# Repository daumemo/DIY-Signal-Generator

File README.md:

# DIY-Signal-Generator

A device, used for generating electrical signals. More infromation: https://daumemo.com/finished-diy-portable-wi-fi-function-generator-part-17

Repository includes all files: firmware code, schematics, PCB files.
STL files for the enclosure can be found here: https://www.thingiverse.com/thing:4596954

Device's specification:
- 3.5 inch IPS LCD with capacitive touch panel
- 2200 mAh Li-Po battery
- ESP-32 MCU
- AD9833 for sine and triangle waveform generation (up to 25 MHz)
- Square wave and PWM generated by the MCU (up to 5 MHz)
- The device can be controlled through LCD or WEB interface
- For WEB control, the device can connect to a Wi-Fi or it can create its own Wi-Fi Access Point
- Output signal’s offset range: -8V … +8V
- Output signal’s amplitude range: 0 … 9V (sine, triangle), 0 … 5.5V (square). PWM output: 3V.
- Battery charging time: <2 hours
- Working time (Wi-Fi on, output relay ON, maximum LCD brightness): around 6 hours
- USB Type C port for charging, 2 SMA ports for signal output, 1 ON/OFF switch, LED charging indicator

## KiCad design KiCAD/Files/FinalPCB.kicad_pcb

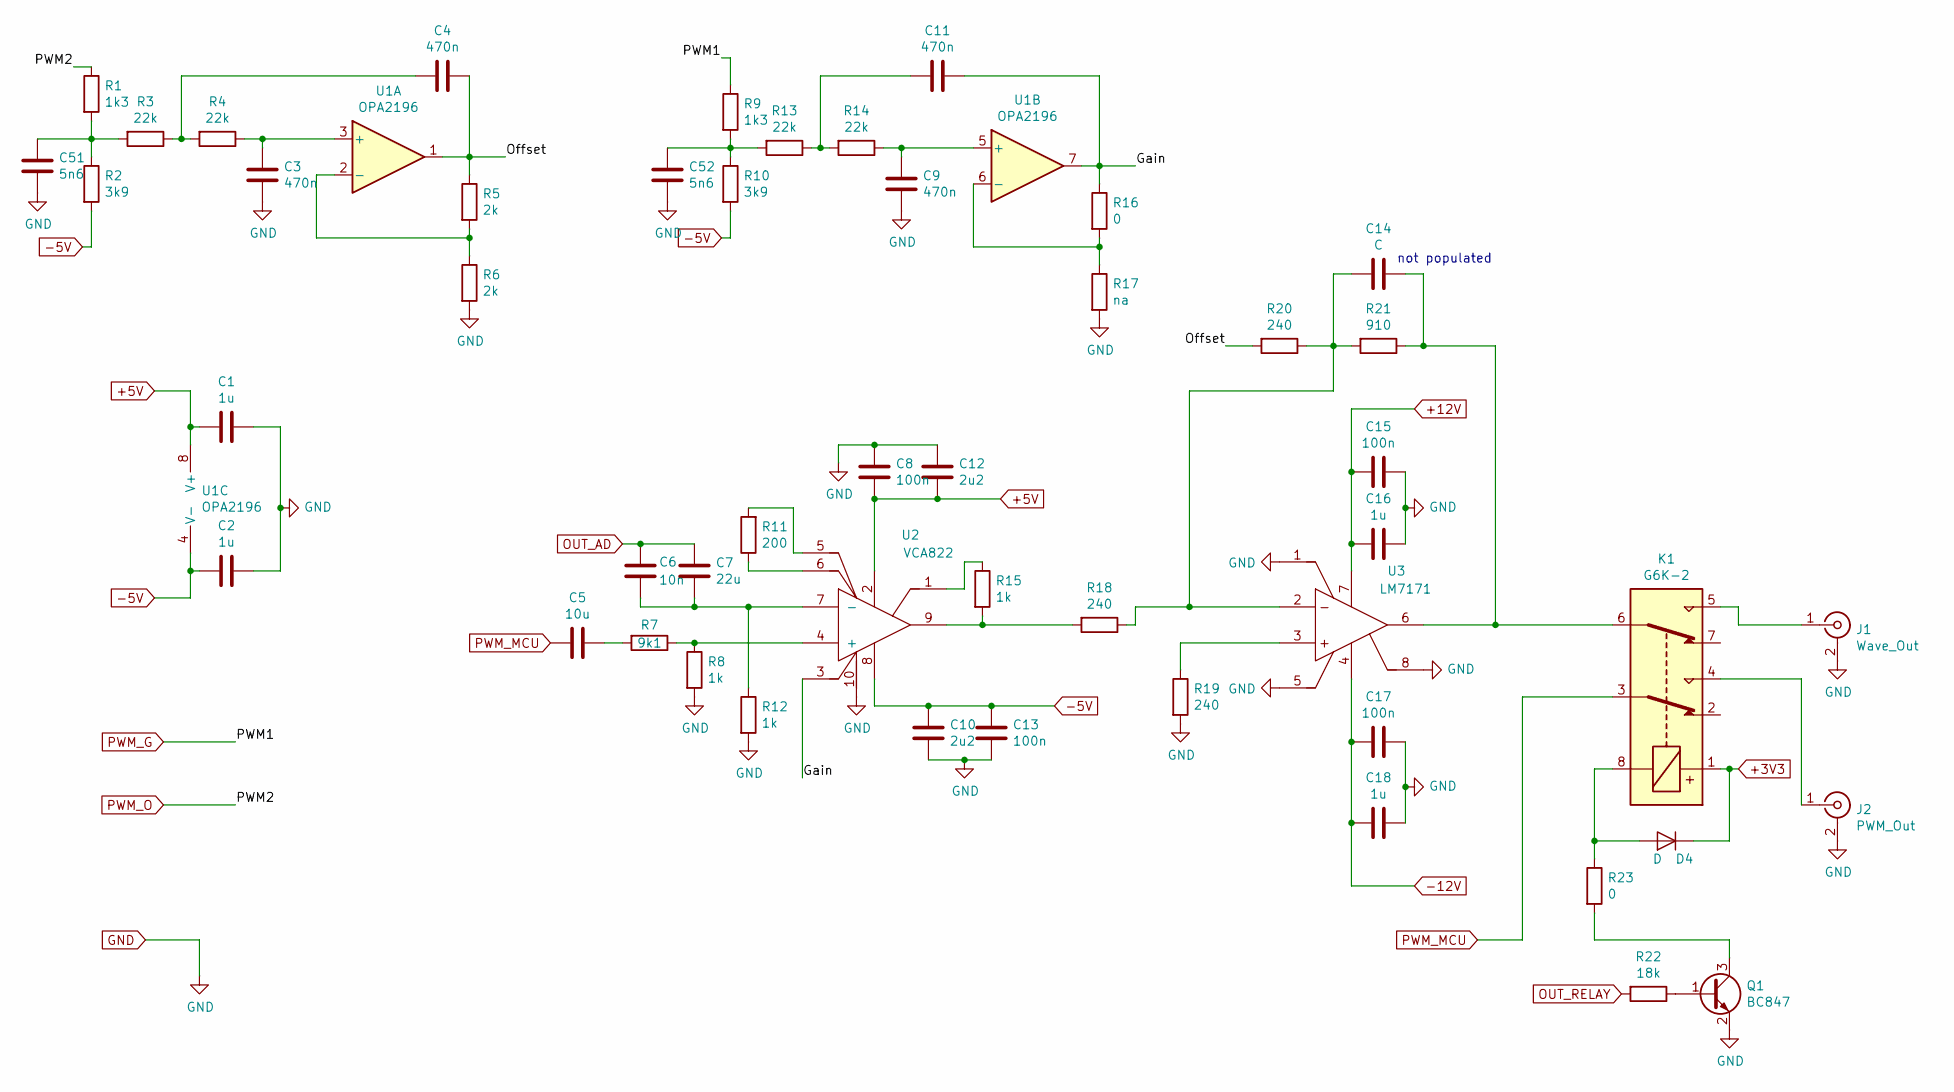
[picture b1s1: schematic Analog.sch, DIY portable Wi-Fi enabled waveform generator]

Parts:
C1, C2, C16, C18: 1u; C_0603
C3, C4, C9, C11: 470n; C_0603
C5: 10u; C_0603
C6: 10n; C_0603
C7: 22u; C_0603
C8, C13, C15, C17: 100n; C_0603
C10, C12: 2u2; C_0603
C14: C; C_0603
C51, C52: 5n6; C_0603
D4: D; D_SOD-123
J1: Wave_Out; SMA_Samtec_SMA-J-P-X-ST-EM1_EdgeMount
J2: PWM_Out; SMA_Samtec_SMA-J-P-X-ST-EM1_EdgeMount
K1: G6K-2; Relay_DPDT_Omron_G6K-2F-Y
Q1: BC847; SOT-23
R1, R9: 1k3; R_0603
R2, R10: 3k9; R_0603
R3, R4, R13, R14: 22k; R_0603
R5, R6: 2k; R_0603
R7: 9k1; R_0603
R8, R12, R15: 1k; R_0603
R11: 200; R_0603
R16: 0; R_0603
R17: na; R_0603
R18, R19, R20: 240; R_0603
R21: 910; R_0603
R22: 18k; R_0603
R23: 0; R_0805
U1: OPA2196; SOIC-8_3.9x4.9mm_Pitch1.27mm
U2: VCA822; MSOP-10_3x3mm_Pitch0.5mm
U3: LM7171; SOIC-8_3.9x4.9mm_Pitch1.27mm

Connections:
+3V3: D4.1 (K), K1.1; also elsewhere on the board
+5V: C1.2, C8.2, C12.2, U1.8 (V+), U2.2; also elsewhere on the board
+12V: C15.2, C16.2, U3.7; also elsewhere on the board
-5V: C2.2, C10.1, C13.1, R2.2, R10.2, U1.4 (V-), U2.8; also elsewhere on the board
-12V: C17.2, C18.2, U3.4; also elsewhere on the board
/Analog/Gain: C11.1, R16.1, U1.7, U2.3
/Analog/Offset: C4.1, R5.1, R20.2, U1.1
GND: C1.1, C2.1, C3.2, C8.1, C9.2, C10.2, C12.1, C13.2, C15.1, C16.1, C17.1, C18.1, C51.2, C52.2, J1.2 (Ext), J2.2 (Ext), Q1.2 (E), R6.2, R8.2, R12.2, R17.2, R19.2, U2.10, U3.1, U3.5, U3.8; also elsewhere on the board
unnamed: C3.1, R4.1, U1.3 (+)
unnamed: C4.2, R3.1, R4.2
unnamed: C5.1, R7.2
unnamed: C6.2, C7.2, R12.1, U2.7 (-)
unnamed: C9.1, R14.1, U1.5 (+)
unnamed: C11.2, R13.1, R14.2
unnamed: C14.1, K1.6, R21.1, U3.6
unnamed: C14.2, R18.1, R20.1, R21.2, U3.2
unnamed: C51.1, R1.2, R2.1, R3.2
unnamed: C52.1, R9.2, R10.1, R13.2
unnamed: D4.2 (A), K1.8, R23.1
unnamed: J1.1 (In), K1.5
unnamed: J2.1 (In), K1.4
unnamed: Q1.1 (B), R22.1
unnamed: Q1.3 (C), R23.2
unnamed: R5.2, R6.1, U1.2 (-)
unnamed: R7.1, R8.1, U2.4 (+)
unnamed: R11.1, U2.6
unnamed: R11.2, U2.5
unnamed: R15.1, U2.1
unnamed: R15.2, R18.2, U2.9
unnamed: R16.2, R17.1, U1.6 (-)
unnamed: R19.1, U3.3
OUT_AD: C6.1, C7.1; also elsewhere on the board
OUT_RELAY: R22.2; also elsewhere on the board
PWM_G: R9.1; also elsewhere on the board
PWM_MCU: C5.2, K1.3; also elsewhere on the board
PWM_O: R1.1; also elsewhere on the board

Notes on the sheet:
not populated

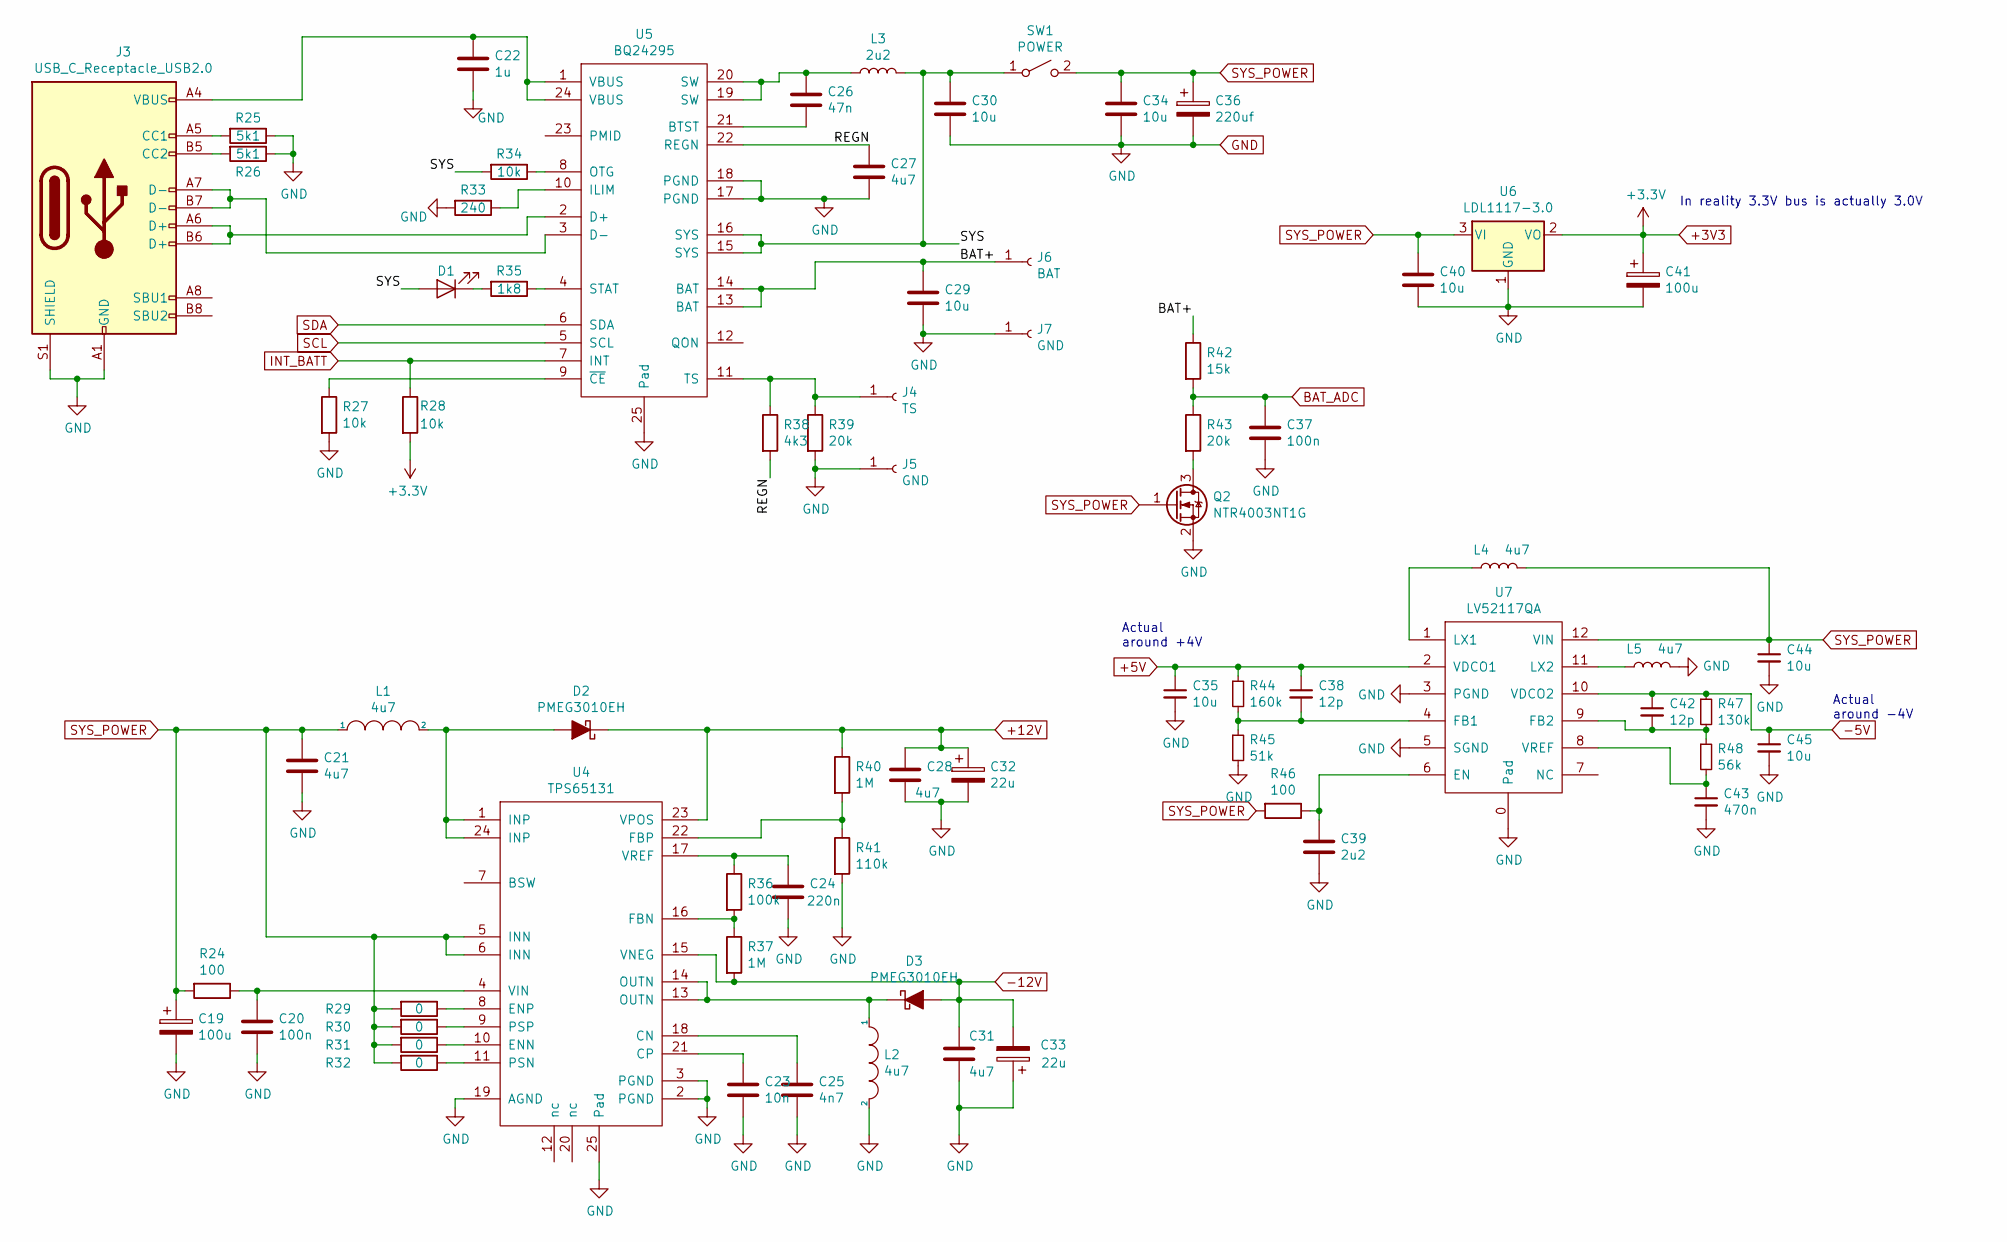
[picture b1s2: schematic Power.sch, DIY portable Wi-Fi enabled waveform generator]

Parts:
C19, C41: 100u; CP_Tantalum_Case-B_EIA-3528-21_Reflow
C20, C37: 100n; C_0603
C21, C27: 4u7; C_0603
C22: 1u; C_0603
C23: 10n; C_0603
C24: 220n; C_0603
C25: 4n7; C_0603
C26: 47n; C_0603
C28, C31: 4u7; C_0805
C29, C30, C34, C35, C40, C44, C45: 10u; C_0603
C32, C33: 22u; CP_Tantalum_Case-B_EIA-3528-21_Reflow
C36: 220uf; CP_Tantalum_Case-C_EIA-6032-28_Reflow
C38, C42: 12p; C_0603
C39: 2u2; C_0603
C43: 470n; C_0603
D1: LED; LED_0603
D2, D3: PMEG3010EH; D_SOD-123
J3: USB_C_Receptacle_USB2.0; HRO-TYPE-C-31-M-12-HandSoldering
J4: TS; Measurement_Point_Square-SMD-Pad_Big
J5, J7: GND; Measurement_Point_Square-SMD-Pad_Big
J6: BAT; Measurement_Point_Square-SMD-Pad_Big
L1, L2, L4, L5: 4u7; L_Taiyo-Yuden_NR-40xx_HandSoldering
L3: 2u2; L_Taiyo-Yuden_NR-40xx_HandSoldering
Q2: NTR4003NT1G; SOT-23
R24, R46: 100; R_0603
R25, R26: 5k1; R_0603
R27, R28, R34: 10k; R_0603
R29, R30, R31, R32: 0; R_0603
R33: 240; R_0603
R35: 1k8; R_0603
R36: 100k; R_0603
R37, R40: 1M; R_0603
R38: 4k3; R_0603
R39, R43: 20k; R_0603
R41: 110k; R_0603
R42: 15k; R_0603
R44: 160k; R_0603
R45: 51k; R_0603
R47: 130k; R_0603
R48: 56k; R_0603
SW1: POWER; Switch
U4: TPS65131; QFN-24-1EP_4x4mm_Pitch0.5mm
U5: BQ24295; QFN-24-1EP_4x4mm_Pitch0.5mm
U6: LDL1117-3.0; SOT-223-3_TabPin2
U7: LV52117QA

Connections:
+3V3: C41.1, R28.2, U6.2 (VO); also elsewhere on the board
+5V: C35.1, C38.1, R44.1, U7.2 (VDCO1); also elsewhere on the board
+12V: C28.1, C32.1, D2.1 (K), R40.1, U4.23 (VPOS); also elsewhere on the board
-5V: C42.1, C45.1, R47.1, U7.10 (VDCO2); also elsewhere on the board
-12V: C31.1, C33.2, D3.2 (A), R37.2, U4.15 (VNEG); also elsewhere on the board
/Power/BAT+: C29.1, J6.1, R42.1, U5.13 (BAT), U5.14 (BAT)
/Power/REGN: C27.1, R38.2, U5.22 (REGN)
/Power/SYS: C30.1, D1.2 (A), L3.2, R34.2, SW1.1 (A), U5.15 (SYS), U5.16 (SYS)
BAT_ADC: C37.1, R42.2, R43.1; also elsewhere on the board
GND: C19.2, C20.2, C21.2, C22.2, C23.2, C24.2, C25.2, C27.2, C28.2, C29.2, C30.2, C31.2, C32.2, C33.1, C34.2, C35.2, C36.2, C37.2, C39.2, C40.2, C41.2, C43.2, C44.2, C45.2, J3.A1 (GND), J3.A12 (GND), J3.B1 (GND), J3.B12 (GND), J3.S1 (SHIELD), J5.1, J7.1, L2.2, L5.2, Q2.2 (S), R25.1, R26.1, R27.2, R33.2, R39.2, R41.2, R45.2, U4.2 (PGND), U4.3 (PGND), U4.19 (AGND), U4.25 (Pad), U5.17 (PGND), U5.18 (PGND), U5.25 (Pad), U6.1 (GND), U7.0 (Pad), U7.3 (PGND), U7.5 (SGND); also elsewhere on the board
INT_BATT: R28.1, U5.7 (INT); also elsewhere on the board
unnamed: C20.1, R24.1, U4.4 (VIN)
unnamed: C22.1, J3.A4 (VBUS), J3.A9 (VBUS), J3.B4 (VBUS), J3.B9 (VBUS), U5.1 (VBUS), U5.24 (VBUS)
unnamed: C23.1, U4.21 (CP)
unnamed: C24.1, R36.1, U4.17 (VREF)
unnamed: C25.1, U4.18 (CN)
unnamed: C26.1, L3.1, U5.19 (SW), U5.20 (SW)
unnamed: C26.2, U5.21 (BTST)
unnamed: C38.2, R44.2, R45.1, U7.4 (FB1)
unnamed: C39.1, R46.1, U7.6 (EN)
unnamed: C42.2, R47.2, R48.1, U7.9 (FB2)
unnamed: C43.1, R48.2, U7.8 (VREF)
unnamed: D1.1 (K), R35.2
unnamed: D2.2 (A), L1.2, U4.1 (INP), U4.24 (INP)
unnamed: D3.1 (K), L2.1, U4.13 (OUTN), U4.14 (OUTN)
unnamed: J3.A5 (CC1), R25.2
unnamed: J3.A6 (D+), J3.B6 (D+), U5.2 (D+)
unnamed: J3.A7 (D-), J3.B7 (D-), U5.3 (D-)
unnamed: J3.B5 (CC2), R26.2
unnamed: J4.1, R38.1, R39.1, U5.11 (TS)
unnamed: L4.1, U7.1 (LX1)
unnamed: L5.1, U7.11 (LX2)
unnamed: Q2.3 (D), R43.2
unnamed: R27.1, U5.9 (~CE)
unnamed: R29.1, U4.8 (ENP)
unnamed: R30.1, U4.9 (PSP)
unnamed: R31.1, U4.10 (ENN)
unnamed: R32.1, U4.11 (PSN)
unnamed: R33.1, U5.10 (ILIM)
unnamed: R34.1, U5.8 (OTG)
unnamed: R35.1, U5.4 (STAT)
unnamed: R36.2, R37.1, U4.16 (FBN)
unnamed: R40.2, R41.1, U4.22 (FBP)
SCL: U5.5 (SCL); also elsewhere on the board
SDA: U5.6 (SDA); also elsewhere on the board
SYS_POWER: C19.1, C21.1, C34.1, C36.1, C40.1, C44.1, L1.1, L4.2, Q2.1 (G), R24.2, R29.2, R30.2, R31.2, R32.2, R46.2, SW1.2 (B), U4.5 (INN), U4.6 (INN), U6.3 (VI), U7.12 (VIN)

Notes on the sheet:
In reality 3.3V bus is actually 3.0V
Actual around -4V
Actual around +4V

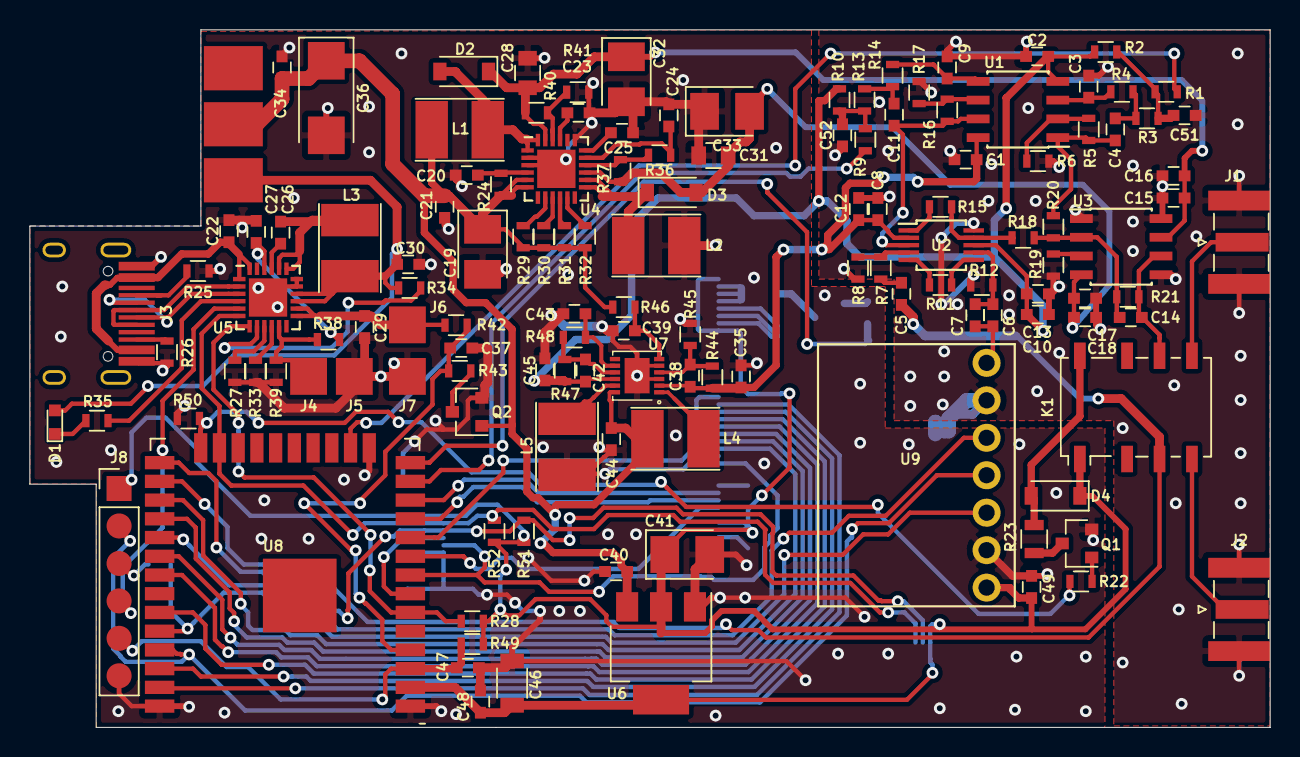
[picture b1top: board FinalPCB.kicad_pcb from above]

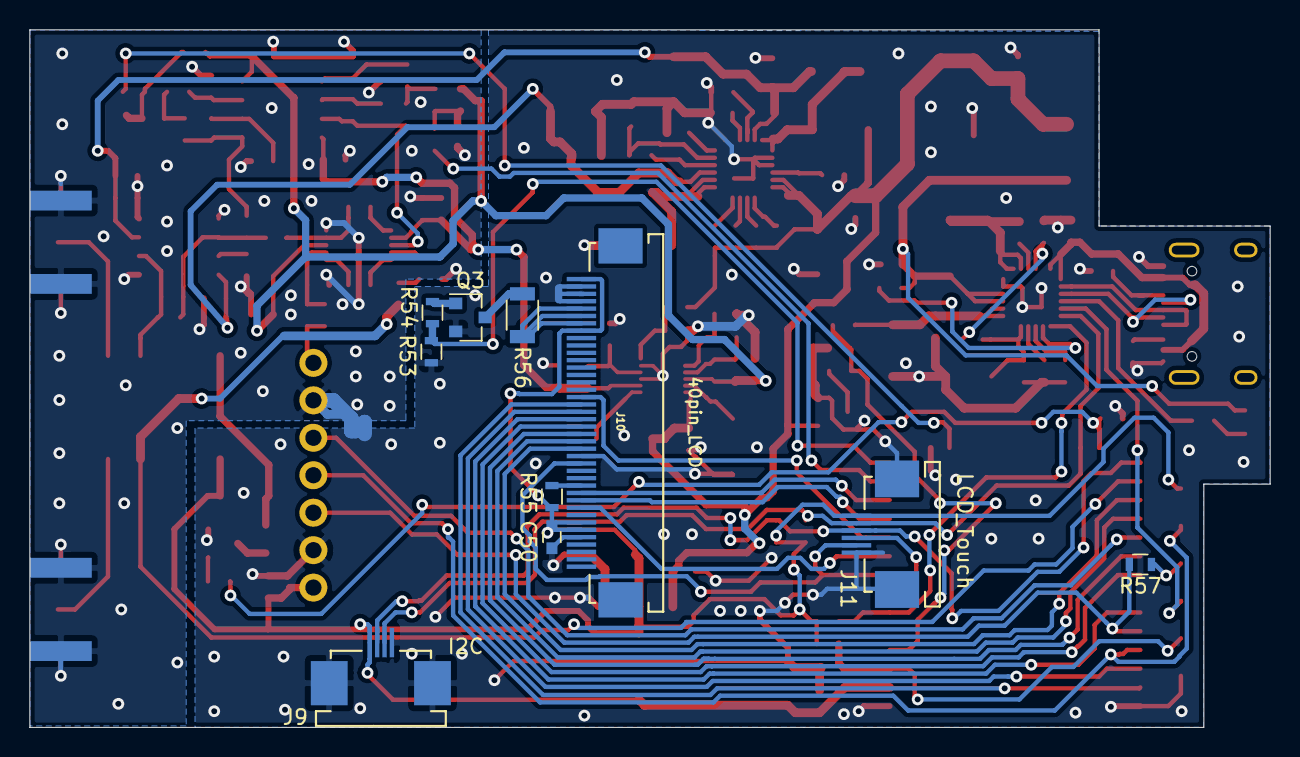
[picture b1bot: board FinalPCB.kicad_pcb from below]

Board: 2 copper layers, 84.1 x 47.3 mm, 143 parts (10 on the bottom side), 99 nets.

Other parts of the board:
C46: 100u; C_1206
C47: 10n; C_0603
C48, C50: 10u; C_0603
C49: 1u; C_0603
J8: UART; Pin_Header_Straight_1x06_Pitch2.54mm
J9: I2C; User_FPC_4pin_05pitch_bot_cont
J10: 40pin_LCD; User_FPC_40pin_05pitch_BottomContact
J11: LCD_Touch; User_FPC_6pin_05pitch_top_cont
Q3: NTR4003NT1G; SOT-23
R49: 12k; R_0603
R50: 10k; R_0603
R51, R52: 3k3; R_0603
R53: 1M; R_0603
R54, R55: 0; R_0603
R56: 1R; R_1206
R57: 470; R_0603
U8: ESP32-WROOM-32
U9: AD9833_module

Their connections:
+3V3: C46.1, C48.1, C49.1, C50.1, J8.1, J9.1, J10.6, J10.7, J10.33, J10.40, J11.1, R49.1, R51.1, R52.1, R55.1, U8.2, U9.1; also elsewhere on the board
/MCU/CSX: J10.9, U8.9
/MCU/D0: J10.17, U8.27
/MCU/D1: J10.18, U8.28
/MCU/D2: J10.19, U8.30
/MCU/D3: J10.20, U8.31
/MCU/D4: J10.21, U8.33
/MCU/D5: J10.22, U8.36
/MCU/D6: J10.23, U8.37
/MCU/D7: J10.24, U8.10
/MCU/DCX: J10.10, U8.11
/MCU/EN: C47.1, J8.5, R49.2, U8.3
/MCU/FSYNC_AD: U8.29, U9.5
/MCU/INT_TOUCH: J11.4, U8.7
/MCU/LED_PWM: R53.1, R54.2, U8.14
/MCU/RDX: J10.12, R55.2
/MCU/RESX: J10.15, J11.5, U8.8
/MCU/RX: R57.2, U8.34, U9.3
/MCU/SCLK_AD: J8.2, U8.35, U9.4
/MCU/WRX: J10.11, U8.12
BAT_ADC: U8.4; also elsewhere on the board
GND: C46.2, C47.2, C48.2, C49.2, C50.2, J8.6, J9.4, J10.5, J10.16, J10.37, J10.38, J10.39, J11.6, Q3.2, R50.2, R53.2, U8.1, U8.15, U8.38, U9.2, U9.6; also elsewhere on the board
INT_BATT: U8.6; also elsewhere on the board
unnamed: J8.3, R57.1
unnamed: J10.34, J10.35, J10.36, R56.1
unnamed: Q3.1, R54.1
unnamed: Q3.3, R56.2
OUT_AD: U9.7; also elsewhere on the board
OUT_RELAY: R50.1, U8.24; also elsewhere on the board
PWM_G: U8.13; also elsewhere on the board
PWM_MCU: U8.26; also elsewhere on the board
PWM_O: U8.16; also elsewhere on the board
SCL: J8.4, J9.2, J11.3, R51.2, U8.25; also elsewhere on the board
SDA: J9.3, J11.2, R52.2, U8.23; also elsewhere on the board

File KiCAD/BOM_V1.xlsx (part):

Date: | 43977.017048611109 | additional modification 2020-09-15
Tool: | Eeschema (5.1.4)-1
NOTE: capacitor voltages specified below are recommended values - it is OK to u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
Component Count: | 141
Ref | Value | Footprint | Description | Remarks, links etc.
C1 | 1u 10V | SMD 0603 | Unpolarized capacitor
C2 | 1u 10V | SMD 0603 | Unpolarized capacitor
C3 | 470n 16V | SMD 0603 | Unpolarized capacitor
C4 | 470n 16V | SMD 0603 | Unpolarized capacitor
C5 | 10uF 6V | SMD 0603 | Unpolarized capacitor
C6 | 10n 50V | SMD 0603 | Unpolarized capacitor
C7 | 22u 6V | SMD 0603 | Unpolarized capacitor
C8 | 100n 50V | SMD 0603 | Unpolarized capacitor
C9 | 470n 16V | SMD 0603 | Unpolarized capacitor
C10 | 2u2 10V | SMD 0603 | Unpolarized capacitor
C11 | 470n 16V | SMD 0603 | Unpolarized capacitor
C12 | 2u2 10V | SMD 0603 | Unpolarized capacitor
C13 | 100n 50V | SMD 0603 | Unpolarized capacitor
C14 | not soldered in | SMD 0603 | Unpolarized capacitor (not soldered in)
C15 | 100n 50V | SMD 0603 | Unpolarized capacitor
C16 | 1u 16V | SMD 0603 | Unpolarized capacitor
C17 | 100n 50V | SMD 0603 | Unpolarized capacitor
C18 | 1u 16V | SMD 0603 | Unpolarized capacitor
C19 | 100u 6V | SMD Case-B (EIA-3528) | Polarized tantalum capacitor
C20 | 100n 50V | SMD 0603 | Unpolarized capacitor
C21 | 4u7 6V | SMD 0603 | Unpolarized capacitor
C22 | 1u 10V | SMD 0603 | Unpolarized capacitor
C23 | 10n 50V | SMD 0603 | Unpolarized capacitor
C24 | 220n 16V | SMD 0603 | Unpolarized capacitor
C25 | 4n7 50V | SMD 0603 | Unpolarized capacitor
C26 | 47n 16V | SMD 0603 | Unpolarized capacitor
C27 | 4u7 6V | SMD 0603 | Unpolarized capacitor
C28 | 4u7 16V | SMD 0805 | Unpolarized capacitor
C29 | 10u 6V | SMD 0603 | Unpolarized capacitor
C30 | 10u 6V | SMD 0603 | Unpolarized capacitor
C31 | 4u7 16V | SMD 0805 | Unpolarized capacitor
C32 | 22u 16V | SMD Case-B (EIA-3528) | Polarized tantalum capacitor
C33 | 22u 16V | SMD Case-B (EIA-3528) | Polarized tantalum capacitor
C34 | 10u 6V | SMD 0603 | Unpolarized capacitor
C35 | 10u 10V | SMD 0603 | Unpolarized capacitor
C36 | 220uf 6V | SMD Case-C (EIA-6032) | Polarized tantalum capacitor
C37 | 100n 50V | SMD 0603 | Unpolarized capacitor
C38 | 12p 50V | SMD 0603 | Unpolarized capacitor
C39 | 2u2 6V | SMD 0603 | Unpolarized capacitor
C40 | 10u 6V | SMD 0603 | Unpolarized capacitor
C41 | 100u 6V | SMD Case-B (EIA-3528) | Polarized tantalum capacitor
C42 | 12p 50V | SMD 0603 | Unpolarized capacitor
C43 | 470n 16V | SMD 0603 | Unpolarized capacitor
C44 | 10u 6V | SMD 0603 | Unpolarized capacitor
C45 | 10u 10V | SMD 0603 | Unpolarized capacitor
C46 | 100u 6V | SMD 1206 | Unpolarized capacitor
C47 | 10n 50V | SMD 0603 | Unpolarized capacitor
C48 | 10u 6V | SMD 0603 | Unpolarized capacitor
C49 | 1u 10V | SMD 0603 | Unpolarized capacitor
C50 | 10u 6V | SMD 0603 | Unpolarized capacitor
C51 | 5n6 25V | SMD 0603 | Unpolarized capacitor
C52 | 5n6 25V | SMD 0603 | Unpolarized capacitor
D1 | LED, amber | SMD LED 0603 | Light emitting diode
D2 | PMEG3010EH | SMD SOD-123 | Schottky diode | Could be used similar diode
D3 | PMEG3010EH | SMD SOD-123 | Schottky diode | Could be used similar diode
D4 | PMEG3010EH | SMD SOD-123 | Diode | Can be a regular diode in SOD-123 case
J1 | Wave_Out | SMA-J-P-X-ST-EM1_EdgeMount | coaxial connector SMA | https://www.aliexpress.com/item/32948380887.html?spm=a2g0s.9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
J2 | PWM_Out | SMA-J-P-X-ST-EM1_EdgeMount | coaxial connector SMA | https://www.aliexpress.com/item/32948380887.html?spm=a2g0s.9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
J3 | USB_C_Receptacle_USB2.0 | Type-C:HRO-TYPE-C-31-M-12-HandSoldering | USB 2.0-only Type-C Receptacle connector | https://www.aliexpress.com/item/32962977859.html?spm=a2g0s.9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
J4 | TS |  | PCB connector
J5 | GND |  | PCB connector
J6 | BAT |  | PCB connector | Lipo/Liion Battery +
J7 | GND |  | PCB connector | Lipo/Liion Battery -
J8 | UART |  | PCB connector
J9 | I2C (not soldered in) | FinalPCB:User_FPC_4pin_05pitch_bot_cont | FPC 4pin connector | Not soldered in (not used)
J10 | 40pin_LCD | FinalPCB:User_FPC_40pin_05pitch_BottomContact | FPC 40pin horizontal bottom contact connector
J11 | LCD_Touch | FinalPCB:User_FPC_6pin_05pitch_top_cont | FPC 6pin horizontal top contact connector
K1 | G6K-2F-Y | Relay_DPDT_Omron_G6K-2F-Y | Miniature 2-pole relay, Single-side Stable
L1 | 4u7 | SMD:4x4mm NRS4012T4R7MDGJ | Inductor | https://eu.mouser.com/ProductDetail/Taiyo-Yuden/NRS4012T4R7M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
L2 | 4u7 | SMD:4x4mm NRS4012T4R7MDGJ | Inductor | https://eu.mouser.com/ProductDetail/Taiyo-Yuden/NRS4012T4R7M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
L3 | 2u2 | SMD:4x4mm NRS4012T2R2MDGJ | Inductor | https://eu.mouser.com/ProductDetail/Taiyo-Yuden/NRS4012T2R2M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
L4 | 4u7 | SMD:4x4mm NRS4012T4R7MDGJ | Inductor | https://eu.mouser.com/ProductDetail/Taiyo-Yuden/NRS4012T4R7M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
L5 | 4u7 | SMD:4x4mm NRS4012T4R7MDGJ | Inductor | https://eu.mouser.com/ProductDetail/Taiyo-Yuden/NRS4012T4R7M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
Q1 | BC847C | SMD SOT-23 | 0.1A Ic, 45V Vce, NPN Transistor, SOT-23
Q2 | NTR4003NT1G | SMD SOT-23 | N-MOSFET transistor, gate/source/drain
Q3 | NTR4003NT1G | SMD SOT-23 | N-MOSFET transistor, gate/source/drain
R1 | 1k3 | SMD 0603 | Resistor
R2 | 3k9 | SMD 0603 | Resistor
R3 | 22k | SMD 0603 | Resistor
R4 | 22k | SMD 0603 | Resistor
R5 | 2k | SMD 0603 | Resistor
R6 | 2k | SMD 0603 | Resistor
R7 | 9k1 | SMD 0603 | Resistor
R8 | 1k | SMD 0603 | Resistor
R9 | 1k3 | SMD 0603 | Resistor
R10 | 3k9 | SMD 0603 | Resistor
R11 | 200 | SMD 0603 | Resistor
R12 | 1k | SMD 0603 | Resistor
R13 | 22k | SMD 0603 | Resistor
R14 | 22k | SMD 0603 | Resistor
R15 | 1k | SMD 0603 | Resistor
R16 | 0 | SMD 0603 | Resistor
R17 | not soldered in | SMD 0603 | Resistor
R18 | 240 | SMD 0603 | Resistor
R19 | 240 | SMD 0603 | Resistor
R20 | 240 | SMD 0603 | Resistor
R21 | 910 | SMD 0603 | Resistor
R22 | 18k | SMD 0603 | Resistor
R23 | 0 | SMD 0805 | Resistor
R24 | 100 | SMD 0603 | Resistor
R25 | 5k1 | SMD 0603 | Resistor
R26 | 5k1 | SMD 0603 | Resistor
R27 | 10k | SMD 0603 | Resistor
R28 | 10k | SMD 0603 | Resistor
R29 | 0 | SMD 0603 | Resistor
R30 | 0 or not soldered | SMD 0603 | Resistor | if soldered in - power saving mode
R31 | 0 | SMD 0603 | Resistor
R32 | 0 or not soldered | SMD 0603 | Resistor | if soldered in - power saving mode
R33 | 240 | SMD 0603 | Resistor
R34 | 10k | SMD 0603 | Resistor
R35 | 1k8 | SMD 0603 | Resistor
R36 | 100k | SMD 0603 | Resistor
R37 | 1M | SMD 0603 | Resistor
R38 | 4k3 | SMD 0603 | Resistor
R39 | 20k | SMD 0603 | Resistor
R40 | 1M | SMD 0603 | Resistor
R41 | 110k | SMD 0603 | Resistor
R42 | 15k | SMD 0603 | Resistor
R43 | 20k | SMD 0603 | Resistor
R44 | 160k | SMD 0603 | Resistor
R45 | 51k | SMD 0603 | Resistor
R46 | 100 | SMD 0603 | Resistor
R47 | 130k | SMD 0603 | Resistor
R48 | 56k | SMD 0603 | Resistor
R49 | 12k | SMD 0603 | Resistor
R50 | 10k | SMD 0603 | Resistor
R51 | 3k3 | SMD 0603 | Resistor
R52 | 3k3 | SMD 0603 | Resistor
R53 | 1M | SMD 0603 | Resistor
R54 | 0 | SMD 0603 | Resistor
R55 | 0 | SMD 0603 | Resistor
R56 | 1R | SMD 1206 | Resistor
R57 | 470 | SMD 0603 | Resistor
SW1 |  | FinalPCB:Switch | Single Pole Single Throw (SPST) switch | https://www.aliexpress.com/item/32852841524.html?spm=a2g0o.d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
U1 | OPA2196 | SOIC:SOIC-8_3.9x4.9mm_Pitch1.27mm | Dual SoundPlus High Performance Audio Operational Amplifiers SOIC-8
U2 | VCA822 | SSOP:MSOP-10_3x3mm_Pitch0.5mm | Variable gain operational amplifier
U3 | LM7171 | SOIC:SOIC-8_3.9x4.9mm_Pitch1.27mm | High bandwidth operational amplifier
U4 | TPS65131 | QFN-24-1EP_4x4mm_Pitch0.5mm | DC-DC converter
U5 | BQ24295 | QFN-24-1EP_4x4mm_Pitch0.5mm | Battery charging IC
U6 | LDL1117-3.0 | SOT-223-3_TabPin2 | 1A Fixed LDO Linear Regulator, 3.0V SOT-223
U7 | LV52117QA | LV52117:LV52117QA | DC-DC converter
U8 | ESP32-WROOM-32 | ESP32-WROOM-32 | RF Module, ESP32-D0WDQ6 SoC, Wi-Fi 802.11b/g/n, Bluetooth, BLE, 32-bit, 2.7-3.6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 | https://www.aliexpress.com/item/32799985552.html?spm=a2g0s.9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
U9 | AD9833_module | AD9833_module |  | https://www.aliexpress.com/item/32998169276.html?spm=a2g0o.p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
EXTERNAL COMPONENTS:
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
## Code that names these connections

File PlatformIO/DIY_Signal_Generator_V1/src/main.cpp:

/************************************************************************************
 * 
 * This is an example code used to test R61529 based LCD with FT6236 touch controller
 * connected to an ESP32 MCU through parallel(8080) interface. This code uses eSPI 
 * library
 * 
 * 
 * Note: Although you will find some files that contains R61581 in it, but be aware 
 * that those are modified files from original eSPI library to support R61529 ICs
 * (Some or all code was changed in those header files).
 * 
 * LCD Connection to the ESP32:
 * 
 * D0 -> GPIO 16
 * D1 -> GPIO 17
 * D2 -> GPIO 18
 * D3 -> GPIO 19
 * D4 -> GPIO 21
 * D5 -> GPIO 22
 * D6 -> GPIO 23
 * D7 -> GPIO 25
 * 
 * CSX -> GPIO 33
 * DCX -> GPIO 26
 * RSX -> GPIO 32
 * WRX -> GPIO 27
 * 
 * TOUCH IC connection to the ESP32:
 * 
 * SDA -> GPIO 15
 * SCL -> GPIO 14->0
 * INT -> GPIO 35
 * RST -> GPIO 32 (connected together with the LCD reset pin) 
 *
 *************************************************************************************/


#include <Arduino.h>

#include "../lib/TFT_eSPI/TFT_eSPI.h"
#include "Wire.h"

#include <WiFi.h>
#include <WiFiUdp.h>
#include <ArduinoOTA.h>
#include "ota.h"
#include <EEPROM.h>
#include <WiFiClient.h>
#include <WebServer.h>
#include <HTTPClient.h>

#include <SPI.h>

#include "../lib/AD9833/ad9833.h"
#include "bq24295.h"
#include "../lib/lvgl/src/lvgl.h"

#include "../lib/lcd_interface/lcd_interface.h"
#include "../lib/touch_drv/touch_drv.h"
#include "../lib/generator/generator.h"
#include "../lib/device/device.h"


uint64_t battMeasureTimer = 0;
int battUpdateTimer = 0;


void setup()
{
  
  Device.LoadSettings();
  
  if(Device.IsApOn() || Device.IsWiFiOn()){
    OtaSetup();
  }

  BQ24295_IC charger(15, 0, 100000);

  charger.setI2cWatchdogTimer(0);
  charger.setFastChargeCurrent(0b010000);
  charger.setPreChargeCurrent(0b0001);
  charger.setFastChargeTimer(0);
  charger.setBoostVoltage(0b1000);
  charger.enableOTG(false);

  
  touchInit();
  Wire.beginTransmission(0x38);
  Wire.write(0xA4);
  Wire.write(0x00); //turn on interrupt
  Wire.endTransmission();

  
  interface_init(); //initialise lcd interface: eSPI and lvgl
  
  Device.MeasureBattery();
  interface_update_battery();

}

void loop()
{
  
  OtaHandleRequests();

  Device.ServerHandlesClient();
  lv_task_handler(); /* let the GUI do its work */
 
  delay(1);
  battMeasureTimer++;
  if(battMeasureTimer > 1000){
    battMeasureTimer = 0;
    Device.MeasureBattery();
    if(battUpdateTimer > 5){
      battUpdateTimer = 0;
      interface_update_battery();
    }
    else {
      battUpdateTimer++;
    }
  }
}

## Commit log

2020-09-15 Initial commit
    Initial commit
